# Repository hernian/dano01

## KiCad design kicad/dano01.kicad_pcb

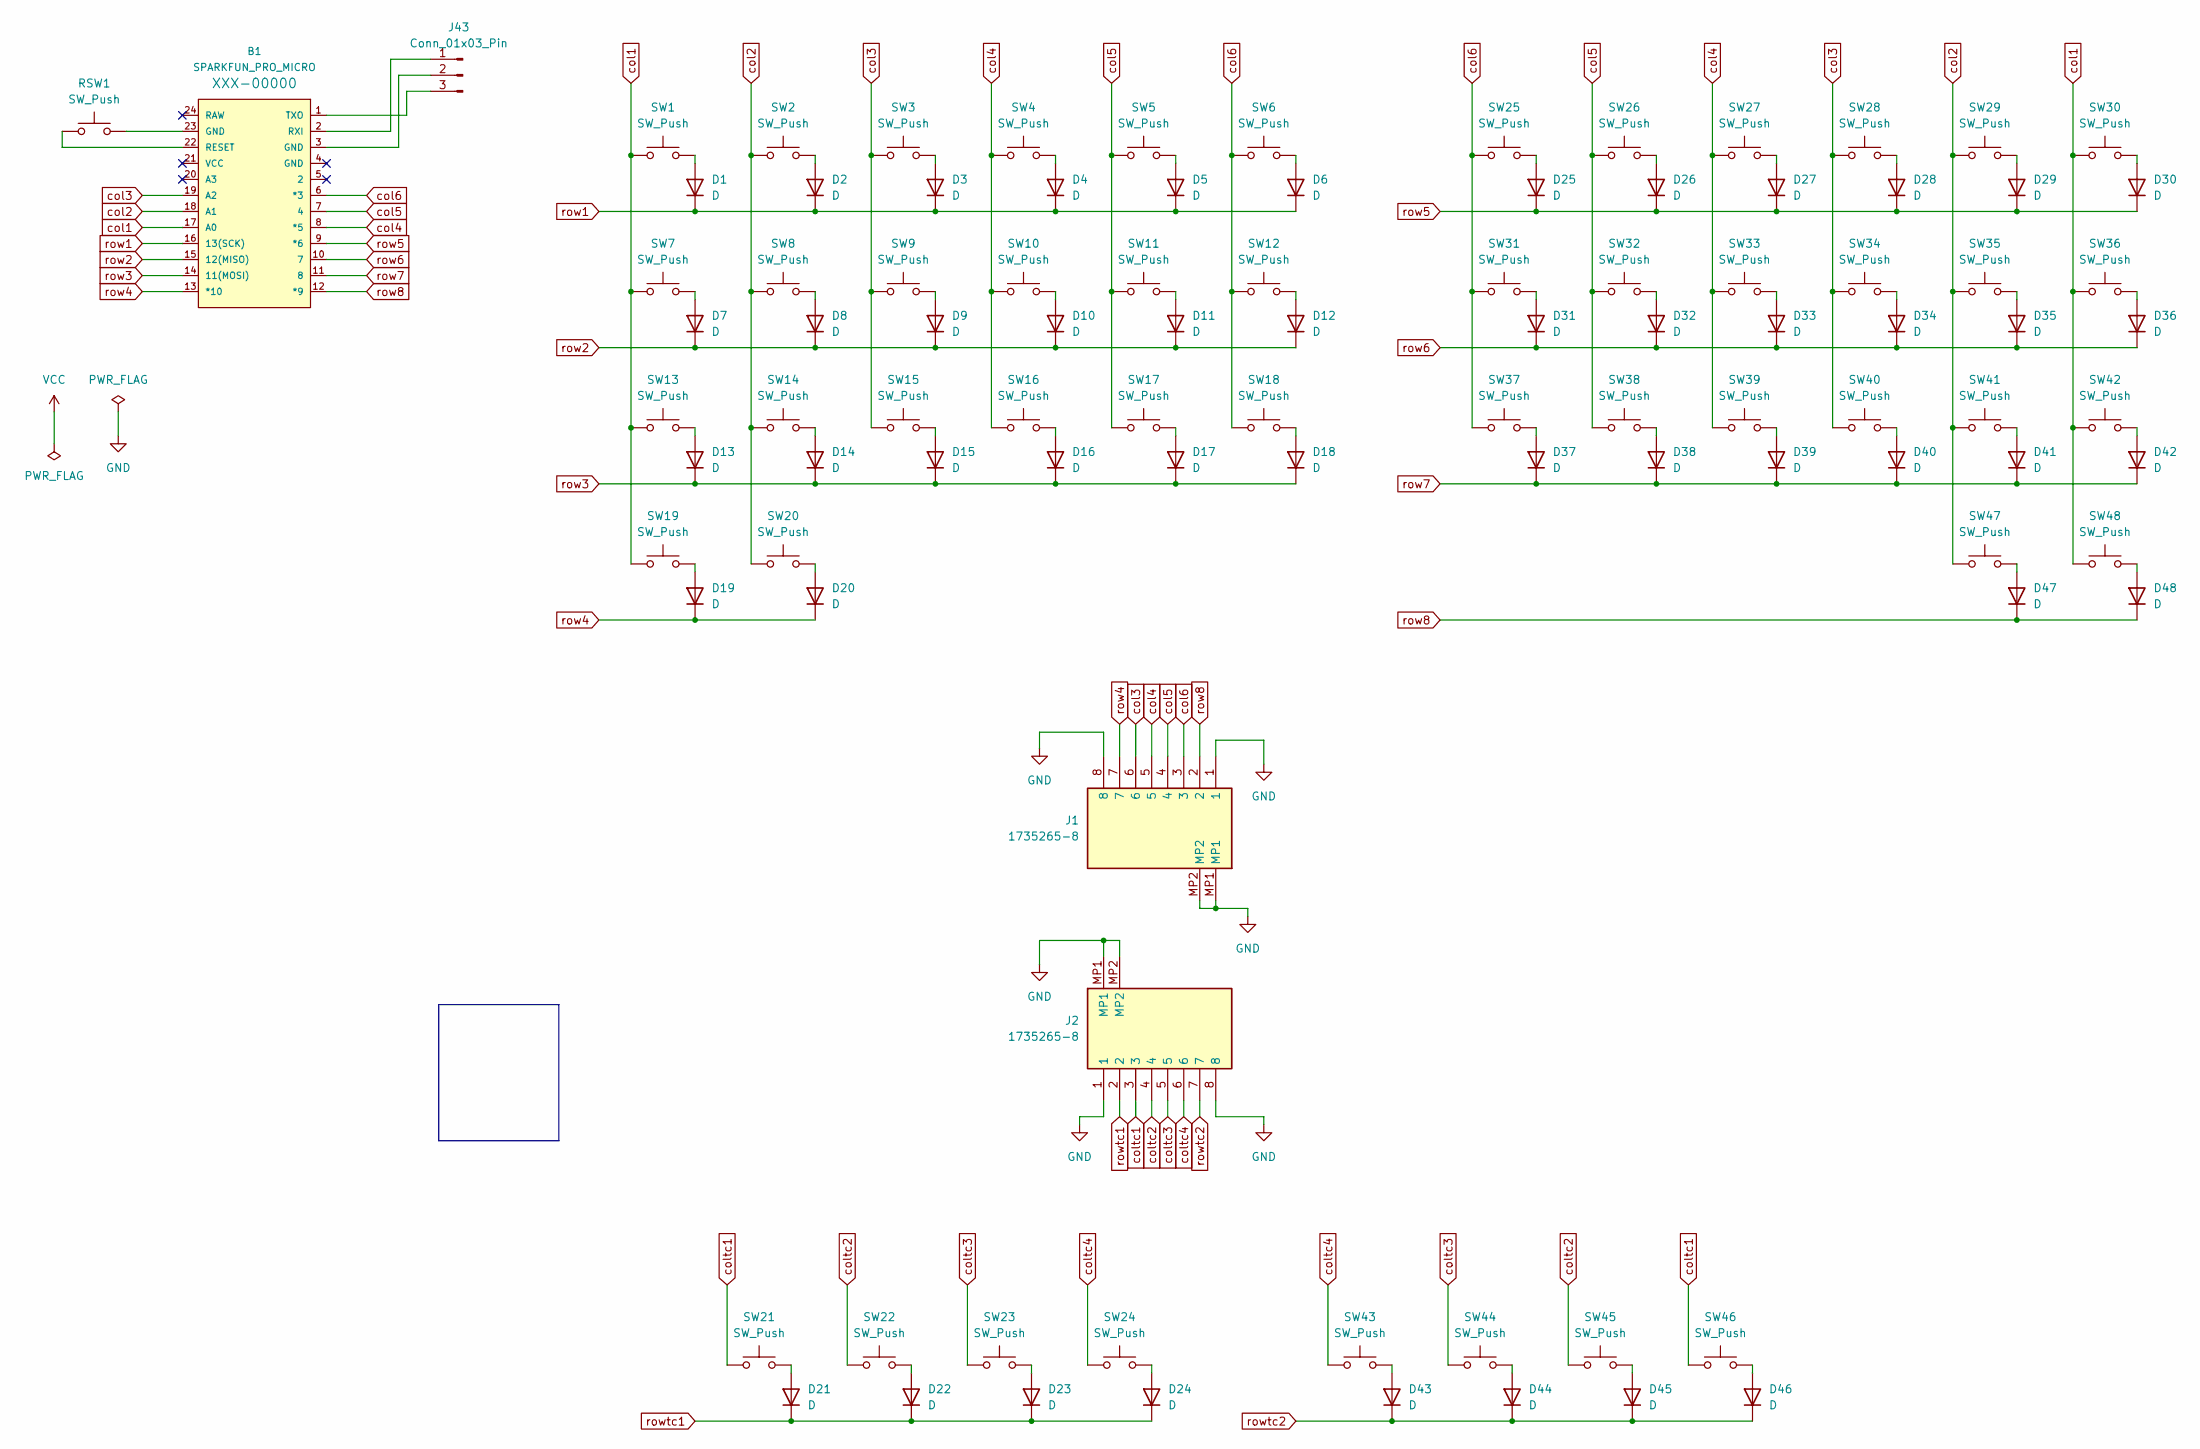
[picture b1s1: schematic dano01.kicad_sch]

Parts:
B1: SPARKFUN_PRO_MICRO; pro_micro_end_th
D1, D2, D3, D4, D5, D6, D7, D8, D9, D10, D11, D12, D13, D14, D15, D16, D17, D18, D19, D20, D21, D22, D23, D24, D25, D26, D27, D28, D29, D30, D31, D32, D33, D34, D35, D36, D37, D38, D39, D40, D41, D42, D43, D44, D45, D46, D47, D48: D; D3_TH
J1, J2: 1735265-8; 17352658; Manufacturer_Part_Number 1735265-8
J43: Conn_01x03_Pin; PinHeader_1x03_P2.54mm_Vertical
RSW1: SW_Push; ResetSW_1side
SW1, SW2, SW3, SW4, SW5, SW6, SW7, SW8, SW9, SW10, SW11, SW12, SW13, SW14, SW15, SW16, SW17, SW18, SW19, SW20, SW21, SW22, SW23, SW24, SW25, SW26, SW27, SW28, SW29, SW30, SW31, SW32, SW33, SW34, SW35, SW36, SW37, SW38, SW39, SW40, SW41, SW42, SW43, SW44, SW45, SW46, SW47, SW48: SW_Push; Kailh_socket_MX

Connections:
GND: J1.1, J1.8, J1.MP1, J1.MP2, J2.1, J2.8, J2.MP1, J2.MP2
unnamed: B1.23 (GND), RSW1.2
unnamed: B1.22 (RESET), RSW1.1
unnamed: B1.2 (RXI), J43.1
unnamed: B1.1 (TXO), J43.3
unnamed: D1.2 (A), SW1.2
unnamed: D2.2 (A), SW2.2
unnamed: D3.2 (A), SW3.2
unnamed: D4.2 (A), SW4.2
unnamed: D5.2 (A), SW5.2
unnamed: D6.2 (A), SW6.2
unnamed: D7.2 (A), SW7.2
unnamed: D8.2 (A), SW8.2
unnamed: D9.2 (A), SW9.2
unnamed: D10.2 (A), SW10.2
unnamed: D11.2 (A), SW11.2
unnamed: D12.2 (A), SW12.2
unnamed: D13.2 (A), SW13.2
unnamed: D14.2 (A), SW14.2
unnamed: D15.2 (A), SW15.2
unnamed: D16.2 (A), SW16.2
unnamed: D17.2 (A), SW17.2
unnamed: D18.2 (A), SW18.2
unnamed: D19.2 (A), SW19.2
unnamed: D20.2 (A), SW20.2
unnamed: D21.2 (A), SW21.2
unnamed: D22.2 (A), SW22.2
unnamed: D23.2 (A), SW23.2
unnamed: D24.2 (A), SW24.2
unnamed: D25.2 (A), SW25.2
unnamed: D26.2 (A), SW26.2
unnamed: D27.2 (A), SW27.2
unnamed: D28.2 (A), SW28.2
unnamed: D29.2 (A), SW29.2
unnamed: D30.2 (A), SW30.2
unnamed: D31.2 (A), SW31.2
unnamed: D32.2 (A), SW32.2
unnamed: D33.2 (A), SW33.2
unnamed: D34.2 (A), SW34.2
unnamed: D35.2 (A), SW35.2
unnamed: D36.2 (A), SW36.2
unnamed: D37.2 (A), SW37.2
unnamed: D38.2 (A), SW38.2
unnamed: D39.2 (A), SW39.2
unnamed: D40.2 (A), SW40.2
unnamed: D41.2 (A), SW41.2
unnamed: D42.2 (A), SW42.2
unnamed: D43.2 (A), SW43.2
unnamed: D44.2 (A), SW44.2
unnamed: D45.2 (A), SW45.2
unnamed: D46.2 (A), SW46.2
unnamed: D47.2 (A), SW47.2
unnamed: D48.2 (A), SW48.2
unnamed: B1.3 (GND), J43.2
col1: B1.17 (A0), SW1.1, SW7.1, SW13.1, SW19.1, SW30.1, SW36.1, SW42.1, SW48.1
col2: B1.18 (A1), SW2.1, SW8.1, SW14.1, SW20.1, SW29.1, SW35.1, SW41.1, SW47.1
col3: B1.19 (A2), J1.6, SW3.1, SW9.1, SW15.1, SW28.1, SW34.1, SW40.1
col4: B1.8 (*5), J1.5, SW4.1, SW10.1, SW16.1, SW27.1, SW33.1, SW39.1
col5: B1.7 (4), J1.4, SW5.1, SW11.1, SW17.1, SW26.1, SW32.1, SW38.1
col6: B1.6 (*3), J1.3, SW6.1, SW12.1, SW18.1, SW25.1, SW31.1, SW37.1
coltc1: J2.3, SW21.1, SW46.1
coltc2: J2.4, SW22.1, SW45.1
coltc3: J2.5, SW23.1, SW44.1
coltc4: J2.6, SW24.1, SW43.1
row1: B1.16 (13(SCK)), D1.1 (K), D2.1 (K), D3.1 (K), D4.1 (K), D5.1 (K), D6.1 (K)
row2: B1.15 (12(MISO)), D7.1 (K), D8.1 (K), D9.1 (K), D10.1 (K), D11.1 (K), D12.1 (K)
row3: B1.14 (11(MOSI)), D13.1 (K), D14.1 (K), D15.1 (K), D16.1 (K), D17.1 (K), D18.1 (K)
row4: B1.13 (*10), D19.1 (K), D20.1 (K), J1.7
row5: B1.9 (*6), D25.1 (K), D26.1 (K), D27.1 (K), D28.1 (K), D29.1 (K), D30.1 (K)
row6: B1.10 (7), D31.1 (K), D32.1 (K), D33.1 (K), D34.1 (K), D35.1 (K), D36.1 (K)
row7: B1.11 (8), D37.1 (K), D38.1 (K), D39.1 (K), D40.1 (K), D41.1 (K), D42.1 (K)
row8: B1.12 (*9), D47.1 (K), D48.1 (K), J1.2
rowtc1: D21.1 (K), D22.1 (K), D23.1 (K), D24.1 (K), J2.2
rowtc2: D43.1 (K), D44.1 (K), D45.1 (K), D46.1 (K), J2.7

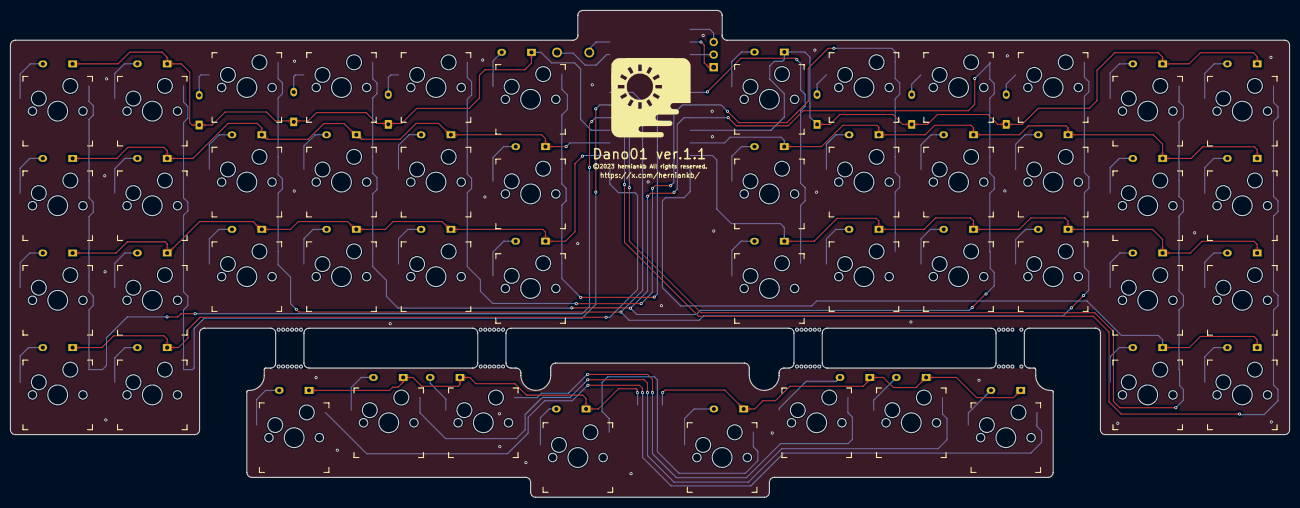
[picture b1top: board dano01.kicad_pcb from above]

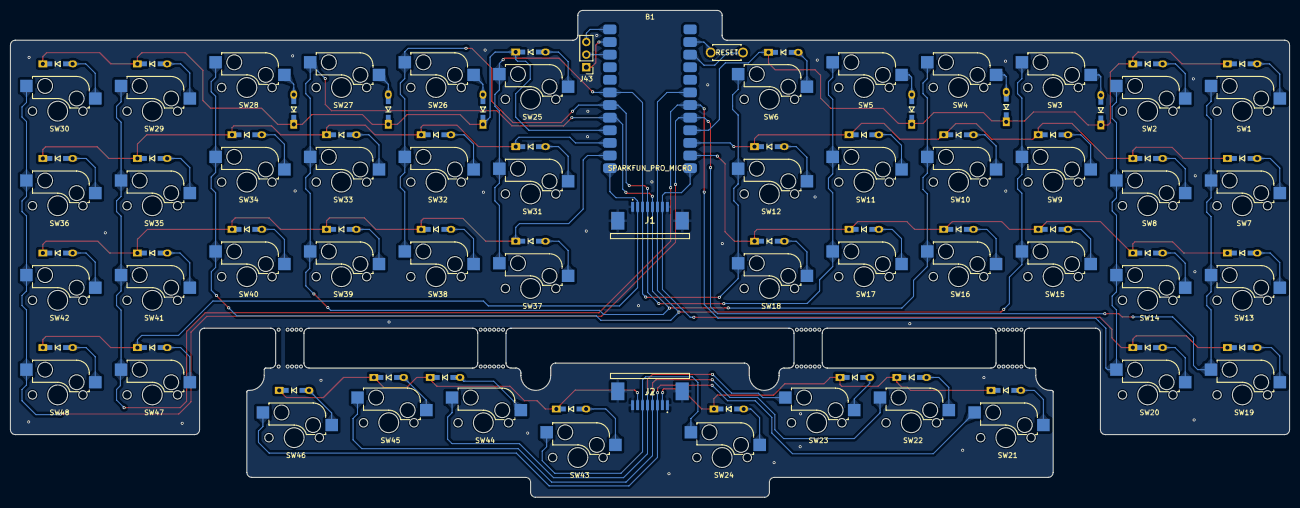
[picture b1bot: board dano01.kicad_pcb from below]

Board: 2 copper layers, 257.7 x 98.1 mm, 101 parts (53 on the bottom side), 74 nets.

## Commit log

2023-12-13 .gitignoreを追加
2023-12-13 kicadプロジェクトとライブラリを初回追加
2023-12-13 PCBアウトラインを追加
2023-12-16 kicadでPCB配線までやった。 FFCコネクタの位置を修正する必要あり。
2023-12-16 PCBアウトラインの更新
2023-12-18 2012/12/18にFusionPCBへ製造依頼をしたもの
2023-12-18 2023/12/18 に FusionPCBへ製造依頼したもの
2023-12-18 FusionPCBへ発注したときのFusion360モデル
2024-01-09 Ver.1.1作業前の変更分
2024-01-09 Ver. 1.1の発注版

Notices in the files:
kicad/dano01.kicad_pcb:
©2023 herniankb All rights reserved.
